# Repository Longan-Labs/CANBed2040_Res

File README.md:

# CANBed2040_Res
Resources for CANBed RP 2040

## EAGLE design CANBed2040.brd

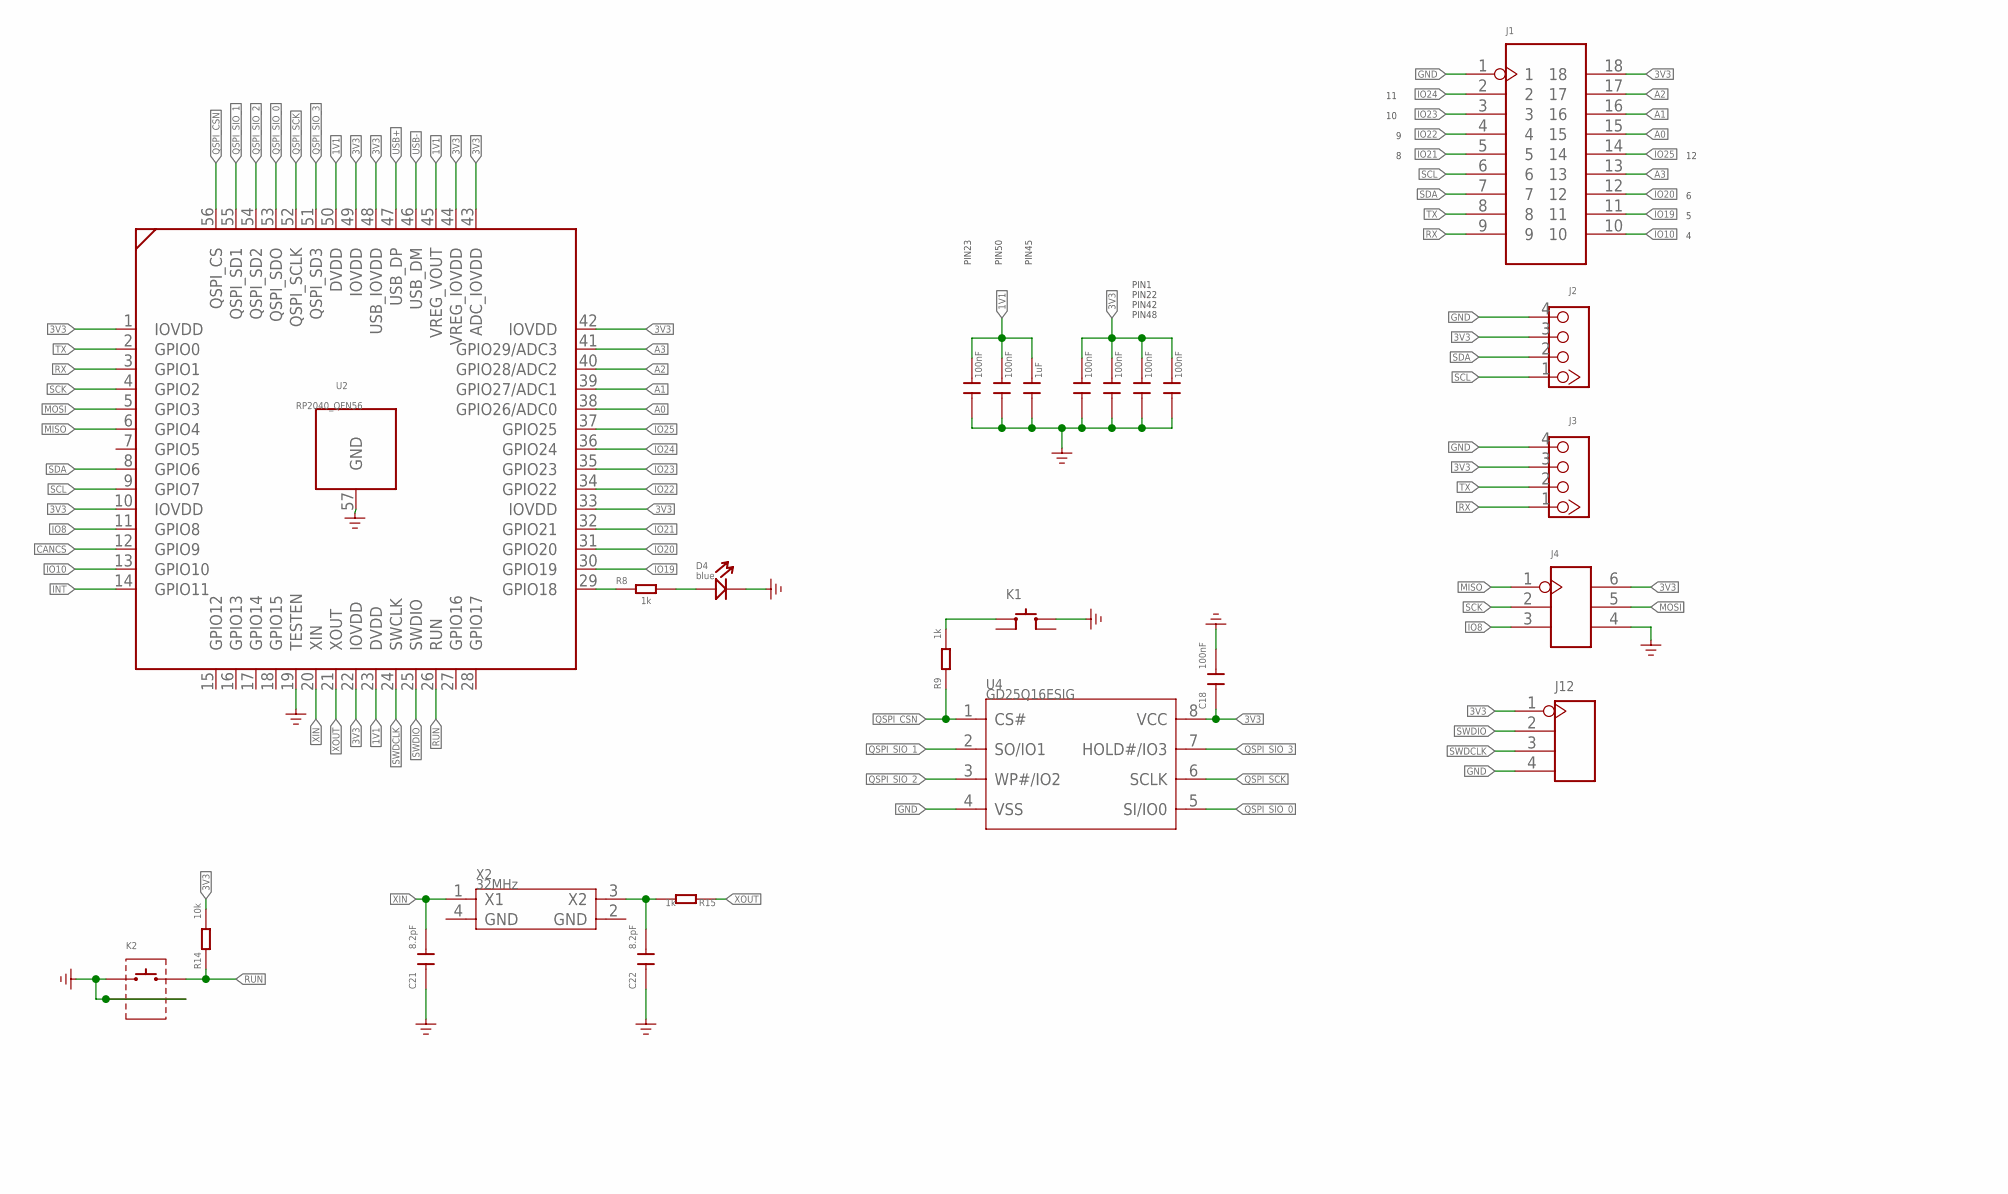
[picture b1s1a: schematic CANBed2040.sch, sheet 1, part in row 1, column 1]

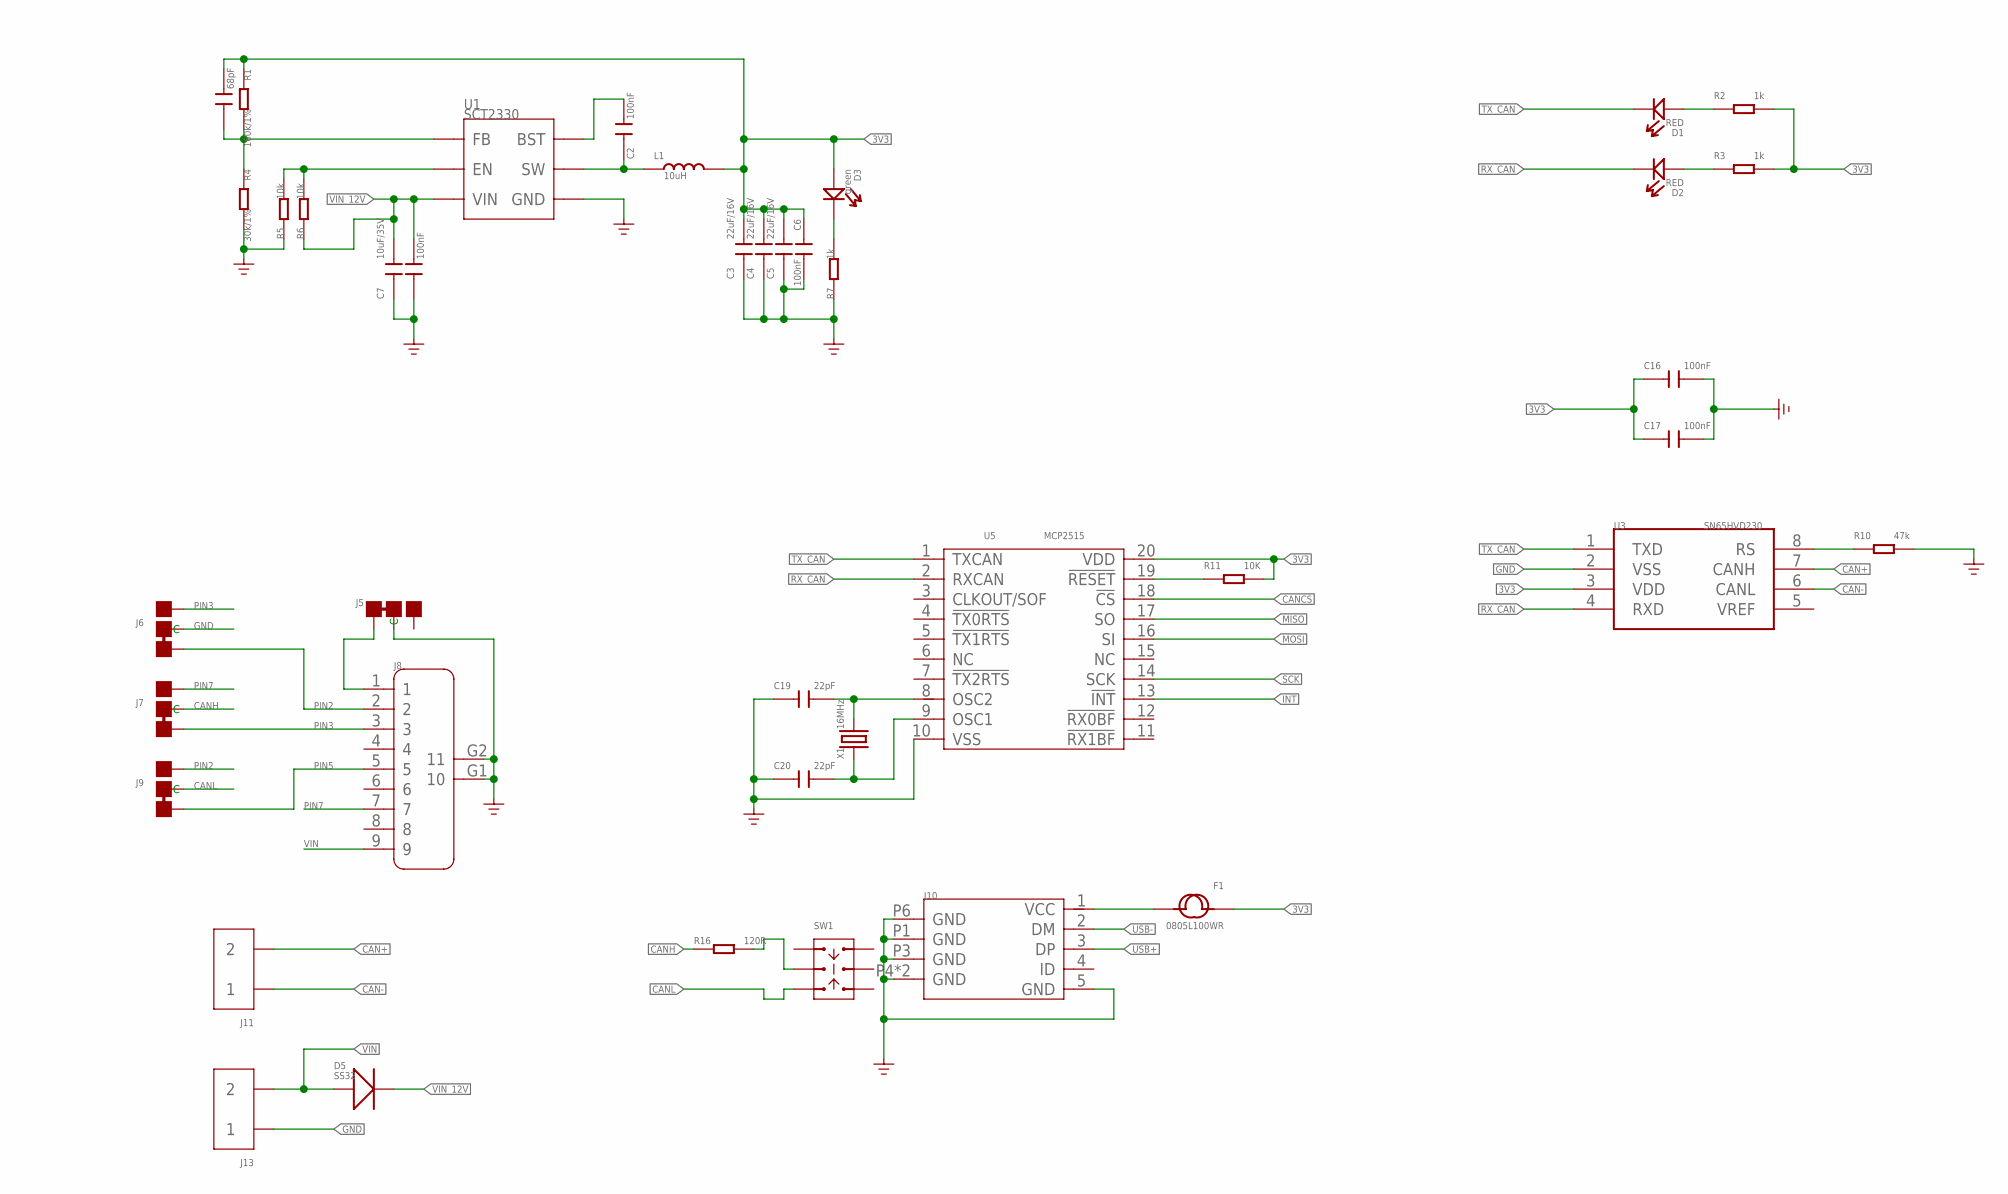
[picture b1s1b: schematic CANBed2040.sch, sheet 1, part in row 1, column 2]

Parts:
C1: 68pF; C0603
C2, C6, C8, C9, C10, C12, C13, C14, C15, C16, C17, C18: 100nF; C0603
C3, C4, C5: 22uF/16V; C0805
C7: 10uF/35V; C1206
C11: 1uF; C0603
C19, C20: 22pF; C0603
C21, C22: 8.2pF; C0603
D1, D2: RED; LED-0603
D3: green; LED-0603
D4: blue; LED-0603
D5: SS32; DO-214AC
F1: 0805L100WR; F0805
J1: HEADER-2X9P-2.54; H2X9-2.54
J2, J3: 320110033; HW4-2.0
J4: HEADER-2X3P-2.54; H2X3-2.54
J5, J6, J7, J9: JUMPER-3P-SHORT; 3P-SMD-SHORT
J8: DB9'MEAL'; DB9-MEAL
J10: MICRO-USB5+4P-320010050; MICRO-USB5+5P-SMD-0.65-7.2X5.06MM
J11, J13: SCREW-TERMINAL-2P'5.08'; H2-5.0-10.5X8.0MM
J12: HEADER-4P-65/35MIL; H4-2.54
K1: BUTTON-4P-4.5X4.5; SW4-4.5X4.5X0.5MM
K2: BUTTON-2+2P; SW2+2P-7.7X2.75X3.95MM
L1: 10uH; INT2-SMD-6.6X7.1X3MM
R1: 160k/1%; R0603
R2, R3, R7, R8, R9, R15: 1k; R0603
R4: 30k/1%; R0603
R5, R6, R14: 10k; R0603
R10: 47k; R0603
R11: 10K; R0603
R16: 120R; R0603
SW1: SWITCH-2CH-6P-311010004; SW6-2.54-9.0X3.5X3.2+2.0MM
U1: SCT2330; SOT-23-6
U2: RP2040_QFN56
U3: SN65HVD230; SOIC8-6.0
U4: GD25Q16ESIG; SOP8-1.27-5.3X5.25X2MM
U5: MCP2515; TSSOP20-0.65-6.5X4.4MM
X1: 16MHz; X4-SMD-3.2X2.5X0.7MM
X2: 32MHz; X4-SMD-3.2X2.5X0.7MM

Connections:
1V1: C9.2, C10.2, C11.2, U2.23 (DVDD), U2.45 (VREG_VOUT), U2.50 (DVDD)
3V3: C1.2, C3.2, C4.2, C5.2, C6.1, C12.2, C13.2, C14.2, C15.2, C16.1, C17.1, C18.1, D3.+, F1.1, J1.18, J2.3, J3.3, J4.6, J12.1, L1.2, R1.1, R2.2, R3.2, R11.2, R14.2, U2.1 (IOVDD), U2.10 (IOVDD), U2.22 (IOVDD), U2.33 (IOVDD), U2.42 (IOVDD), U2.43 (ADC_IOVDD), U2.44 (VREG_IOVDD), U2.48 (USB_IOVDD), U2.49 (IOVDD), U3.3 (VDD), U4.8 (VCC), U5.20 (VDD)
A0: J1.15, U2.38 (GPIO26/ADC0)
A1: J1.16, U2.39 (GPIO27/ADC1)
A2: J1.17, U2.40 (GPIO28/ADC2)
A3: J1.13, U2.41 (GPIO29/ADC3)
CAN+: J11.2, U3.7 (CANH)
CAN-: J11.1, U3.6 (CANL)
CANCS: U2.12 (GPIO9), U5.18 (!CS)
CANH: J7.MM (C), R16.1
CANL: J9.MM (C), SW1.CH1B
EXT_PWR: F1.2, J10.1 (VCC)
GND: C3.1, C4.1, C5.1, C6.2, C7.1, C8.1, C9.1, C10.1, C11.1, C12.1, C13.1, C14.1, C15.1, C16.2, C17.2, C18.2, C19.1, C20.1, C21.1, C22.1, D4.-, J1.1, J2.4, J3.4, J4.4, J5.MM (C), J6.MM (C), J8.G1 (10), J8.G2 (11), J10.5 (GND), J10.P1 (GND), J10.P3 (GND), J10.P4 (GND), J10.P5 (GND), J10.P6 (GND), J12.4, J13.1, K1.3 (B0), K2.1, K2.S1, K2.S2, R4.2, R5.1, R7.1, R10.2, U1.4 (GND), U2.19 (TESTEN), U2.57 (GND), U3.2 (VSS), U4.4 (VSS), U5.10 (VSS)
INT: U2.14 (GPIO11), U5.13 (!INT)
IO8: J4.3, U2.11 (GPIO8)
IO10: J1.10, U2.13 (GPIO10)
IO19: J1.11, U2.30 (GPIO19)
IO20: J1.12, U2.31 (GPIO20)
IO21: J1.5, U2.32 (GPIO21)
IO22: J1.4, U2.34 (GPIO22)
IO23: J1.3, U2.35 (GPIO23)
IO24: J1.2, U2.36 (GPIO24)
IO25: J1.14, U2.37 (GPIO25)
MISO: J4.1, U2.6 (GPIO4), U5.17 (SO)
MOSI: J4.5, U2.5 (GPIO3), U5.16 (SI)
unnamed: D3.-, R7.2
unnamed: D1.+, R2.1
unnamed: R8.1, U2.29 (GPIO18)
unnamed: C1.1, R1.2, R4.1, U1.1 (FB)
unnamed: R16.2, SW1.COM1
unnamed: D4.+, R8.2
unnamed: K1.1 (A0), R9.2
unnamed: C22.2, R15.2, X2.3 (X2)
unnamed: R5.2, R6.2, U1.2 (EN)
unnamed: C2.2, U1.6 (BST)
unnamed: J5.11 (L), J8.1
unnamed: D2.+, R3.1
unnamed: C19.2, U5.8 (OSC2), X1.3 (2)
unnamed: C20.2, U5.9 (OSC1), X1.1
unnamed: C2.1, L1.1, U1.5 (SW)
unnamed: R10.1, U3.8 (RS)
PIN2: J6.11 (L), J8.2, J9.00 (R)
PIN3: J6.00 (R), J7.11 (L), J8.3
PIN5: J8.5, J9.11 (L)
PIN7: J7.00 (R), J8.7
QSPI_CSN: R9.1, U2.56 (QSPI_CS), U4.1 (CS#)
QSPI_SCK: U2.52 (QSPI_SCLK), U4.6 (SCLK)
QSPI_SIO_0: U2.53 (QSPI_SDO), U4.5 (SI/IO0)
QSPI_SIO_1: U2.55 (QSPI_SD1), U4.2 (SO/IO1)
QSPI_SIO_2: U2.54 (QSPI_SD2), U4.3 (WP#/IO2)
QSPI_SIO_3: U2.51 (QSPI_SD3), U4.7 (HOLD#/IO3)
RST_N: R11.1, U5.19 (!RESET)
RUN: K2.2, R14.1, U2.26 (RUN)
RX: J1.9, J3.1, U2.3 (GPIO1)
RX_CAN: D2.-, U3.4 (RXD), U5.2 (RXCAN)
SCK: J4.2, U2.4 (GPIO2), U5.14 (SCK)
SCL: J1.6, J2.1, U2.9 (GPIO7)
SDA: J1.7, J2.2, U2.8 (GPIO6)
SWDCLK: J12.3, U2.24 (SWCLK)
SWDIO: J12.2, U2.25 (SWDIO)
TX: J1.8, J3.2, U2.2 (GPIO0)
TX_CAN: D1.-, U3.1 (TXD), U5.1 (TXCAN)
USB+: J10.3 (DP), U2.47 (USB_DP)
USB-: J10.2 (DM), U2.46 (USB_DM)
VIN: D5.1 (+), J8.9, J13.2
VIN_12V: C7.2, C8.2, D5.2 (-), R6.1, U1.3 (VIN)
XIN: C21.2, U2.20 (XIN), X2.1 (X1)
XOUT: R15.1, U2.21 (XOUT)

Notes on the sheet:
PIN1
PIN22
PIN42
PIN48
PIN23
PIN50
PIN45

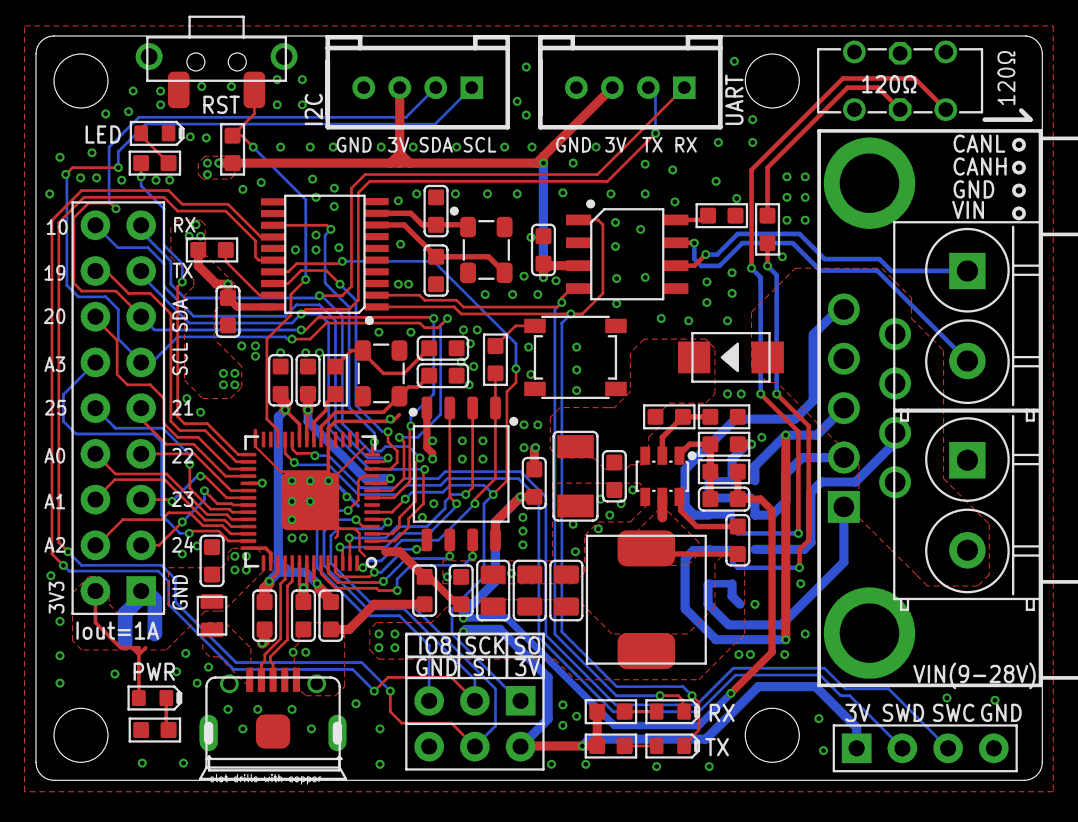
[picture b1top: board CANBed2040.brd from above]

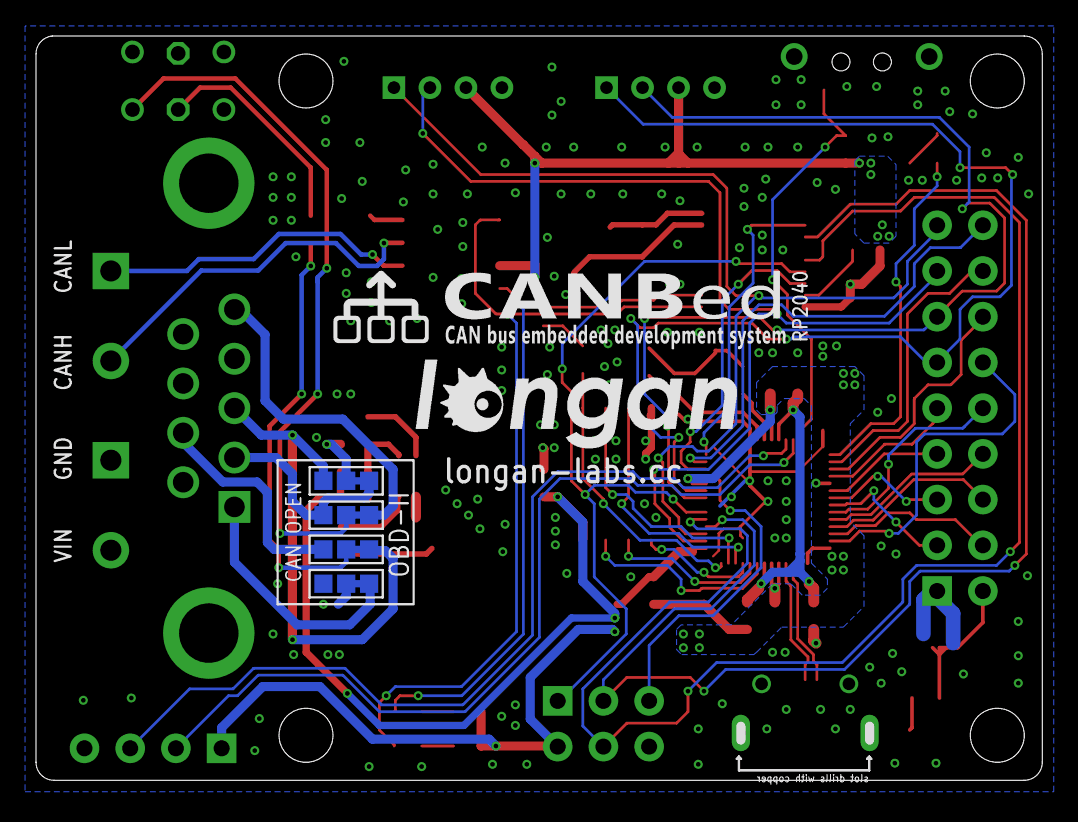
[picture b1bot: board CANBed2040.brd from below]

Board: 2 copper layers, 55.4 x 41.2 mm, 67 parts (5 on the bottom side), 68 nets.

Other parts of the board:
U$12: LONGAN-SILK-SMALL

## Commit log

2021-11-22 add eagle file
